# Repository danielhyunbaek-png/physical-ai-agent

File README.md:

Architecture:

The Physical AI Agent I'm currently building is a closed loop system that is made to operate a computer exactly how a human does. It uses visual feedback and physical actuations. The system runs on a discrete time loop across a macOS host and two microcontrollers.

Vision:

- Uses a fixed webcam
- Python based pipeline will capture frames at 30 fps. Each frame is deskewed using a precomputed perspective transform to map the MacBook screen to a fixed 1920x1200 pixel grid. 
- Uses OpenCV template matching for UI elements and Tesseract OCR for text extraction. 

Cognition: 

- Runs on the MacBook Pro
- Python FSM that reads perception stream and executes serial commands. 
- Goal: Under 100 ms from screen change to first physical actuation. 

Action:

-Keyboard: Using the Nuphy Air75 v3 keyboard with Blush Nano switches (45g force, 1.4 actuation).
Using the Arduino mega 2560 with 84 12V micro solenoids (10mm stroke, 5N force), housed in a custom 3D printed matrix plate. 11 cascaded 74HC595 shift resistors feeding 11 ULN2803A Darlington arrays. All powered by 12V PSU with a firmware cap of 12 solenoid activations. 

Mouse: 2 axis XY gantry system controlled by Arduino Uno. Powered by NEMA 17 steppers driven by A4988 drivers. Two SG90 hobby servos providing click actuation.

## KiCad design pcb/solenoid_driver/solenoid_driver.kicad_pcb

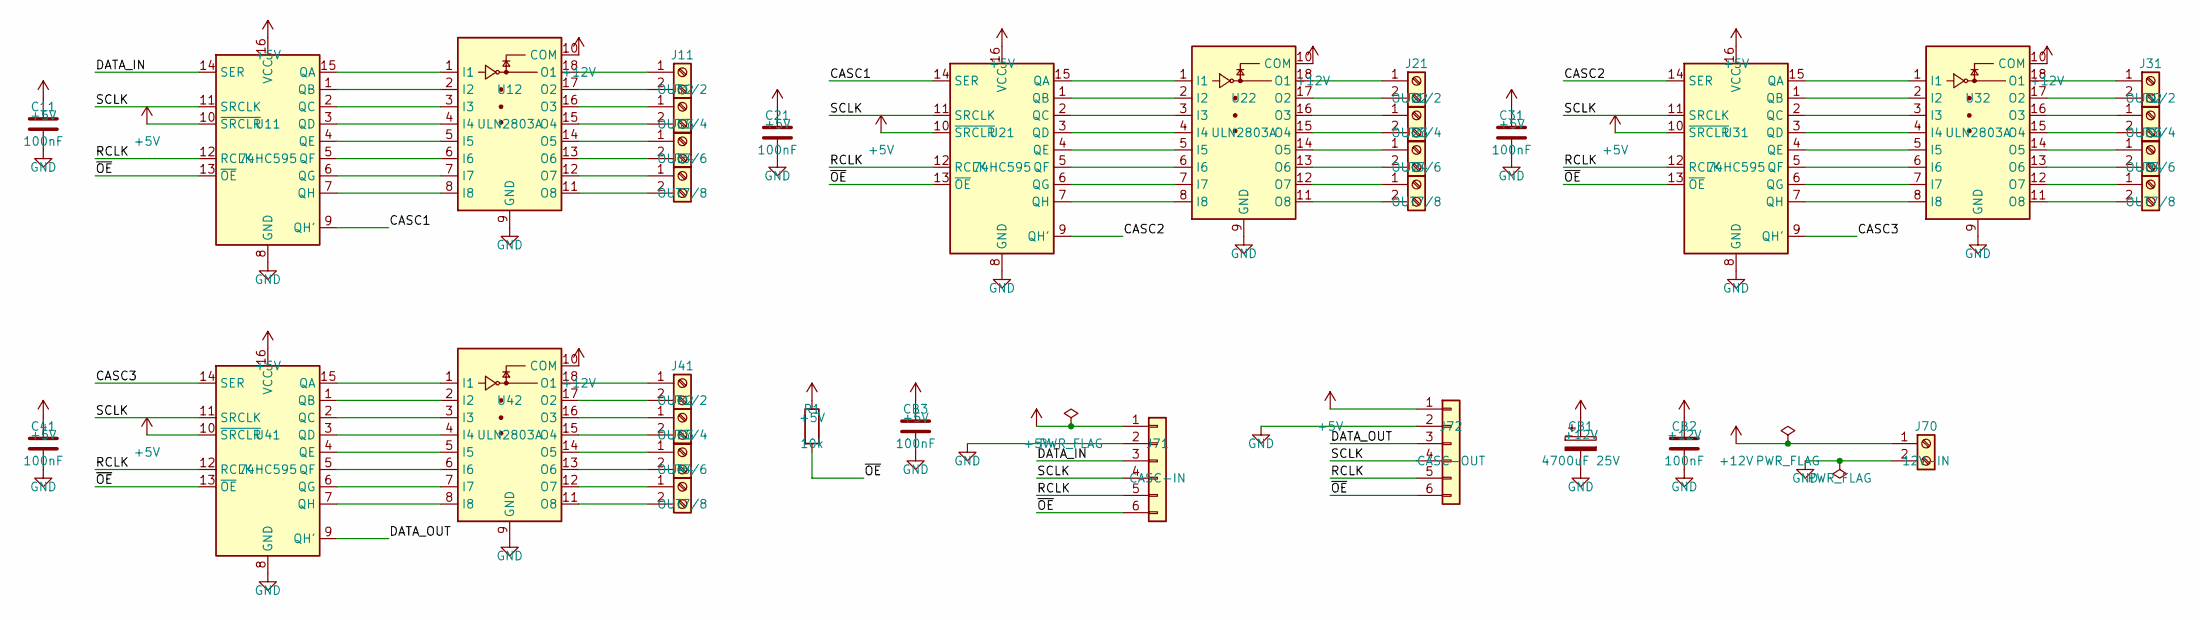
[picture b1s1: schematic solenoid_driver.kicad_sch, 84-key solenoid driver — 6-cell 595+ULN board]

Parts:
C11, C21, C31, C41: 100nF; C_Disc_D8.0mm_W5.0mm_P5.00mm
CB1: 4700uF 25V; CP_Radial_D18.0mm_P7.50mm
CB2, CB3: 100nF; C_Disc_D8.0mm_W5.0mm_P5.00mm
J11, J21, J31, J41: OUT1/2; TerminalBlock_CUI_TB007-508-02_1x02_P5.08mm_Horizontal
J12, J22, J32, J42: OUT3/4; TerminalBlock_CUI_TB007-508-02_1x02_P5.08mm_Horizontal
J13, J23, J33, J43: OUT5/6; TerminalBlock_CUI_TB007-508-02_1x02_P5.08mm_Horizontal
J14, J24, J34, J44: OUT7/8; TerminalBlock_CUI_TB007-508-02_1x02_P5.08mm_Horizontal
J70: 12V-IN; TerminalBlock_CUI_TB007-508-02_1x02_P5.08mm_Horizontal
J71: CASC-IN; PinHeader_1x06_P2.54mm_Vertical
J72: CASC-OUT; PinHeader_1x06_P2.54mm_Vertical
R1: 10k; R_Axial_DIN0207_L6.3mm_D2.5mm_P10.16mm_Horizontal
U11, U21, U31, U41: 74HC595; DIP-16_W7.62mm
U12, U22, U32, U42: ULN2803A; DIP-18_W7.62mm

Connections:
+5V: C11.1, C21.1, C31.1, C41.1, CB3.1, J71.1, J72.1, R1.1, U11.10 (~SRCLR), U11.16 (VCC), U21.10 (~SRCLR), U21.16 (VCC), U31.10 (~SRCLR), U31.16 (VCC), U41.10 (~SRCLR), U41.16 (VCC)
+12V: CB1.1, CB2.1, J70.1, U12.10 (COM), U22.10 (COM), U32.10 (COM), U42.10 (COM)
/CASC1: U11.9 (QH'), U21.14 (SER)
/CASC2: U21.9 (QH'), U31.14 (SER)
/CASC3: U31.9 (QH'), U41.14 (SER)
/DATA_IN: J71.3, U11.14 (SER)
/DATA_OUT: J72.3, U41.9 (QH')
/RCLK: J71.5, J72.5, U11.12 (RCLK), U21.12 (RCLK), U31.12 (RCLK), U41.12 (RCLK)
/SCLK: J71.4, J72.4, U11.11 (SRCLK), U21.11 (SRCLK), U31.11 (SRCLK), U41.11 (SRCLK)
/~OE: J71.6, J72.6, R1.2, U11.13 (~OE), U21.13 (~OE), U31.13 (~OE), U41.13 (~OE)
GND: C11.2, C21.2, C31.2, C41.2, CB1.2, CB2.2, CB3.2, J70.2, J71.2, J72.2, U11.8 (GND), U12.9 (GND), U21.8 (GND), U22.9 (GND), U31.8 (GND), U32.9 (GND), U41.8 (GND), U42.9 (GND)
unnamed: J11.1, U12.18 (O1)
unnamed: J11.2, U12.17 (O2)
unnamed: J12.1, U12.16 (O3)
unnamed: J12.2, U12.15 (O4)
unnamed: J13.1, U12.14 (O5)
unnamed: J13.2, U12.13 (O6)
unnamed: J14.1, U12.12 (O7)
unnamed: J14.2, U12.11 (O8)
unnamed: J21.1, U22.18 (O1)
unnamed: J21.2, U22.17 (O2)
unnamed: J22.1, U22.16 (O3)
unnamed: J22.2, U22.15 (O4)
unnamed: J23.1, U22.14 (O5)
unnamed: J23.2, U22.13 (O6)
unnamed: J24.1, U22.12 (O7)
unnamed: J24.2, U22.11 (O8)
unnamed: J31.1, U32.18 (O1)
unnamed: J31.2, U32.17 (O2)
unnamed: J32.1, U32.16 (O3)
unnamed: J32.2, U32.15 (O4)
unnamed: J33.1, U32.14 (O5)
unnamed: J33.2, U32.13 (O6)
unnamed: J34.1, U32.12 (O7)
unnamed: J34.2, U32.11 (O8)
unnamed: J41.1, U42.18 (O1)
unnamed: J41.2, U42.17 (O2)
unnamed: J42.1, U42.16 (O3)
unnamed: J42.2, U42.15 (O4)
unnamed: J43.1, U42.14 (O5)
unnamed: J43.2, U42.13 (O6)
unnamed: J44.1, U42.12 (O7)
unnamed: J44.2, U42.11 (O8)
unnamed: U11.15 (QA), U12.1 (I1)
unnamed: U11.1 (QB), U12.2 (I2)
unnamed: U11.2 (QC), U12.3 (I3)
unnamed: U11.3 (QD), U12.4 (I4)
unnamed: U11.4 (QE), U12.5 (I5)
unnamed: U11.5 (QF), U12.6 (I6)
unnamed: U11.6 (QG), U12.7 (I7)
unnamed: U11.7 (QH), U12.8 (I8)
unnamed: U21.15 (QA), U22.1 (I1)
unnamed: U21.1 (QB), U22.2 (I2)
unnamed: U21.2 (QC), U22.3 (I3)
unnamed: U21.3 (QD), U22.4 (I4)
unnamed: U21.4 (QE), U22.5 (I5)
unnamed: U21.5 (QF), U22.6 (I6)
unnamed: U21.6 (QG), U22.7 (I7)
unnamed: U21.7 (QH), U22.8 (I8)
unnamed: U31.15 (QA), U32.1 (I1)
unnamed: U31.1 (QB), U32.2 (I2)
unnamed: U31.2 (QC), U32.3 (I3)
unnamed: U31.3 (QD), U32.4 (I4)
unnamed: U31.4 (QE), U32.5 (I5)
unnamed: U31.5 (QF), U32.6 (I6)
unnamed: U31.6 (QG), U32.7 (I7)
unnamed: U31.7 (QH), U32.8 (I8)
unnamed: U41.15 (QA), U42.1 (I1)
unnamed: U41.1 (QB), U42.2 (I2)
unnamed: U41.2 (QC), U42.3 (I3)
unnamed: U41.3 (QD), U42.4 (I4)
unnamed: U41.4 (QE), U42.5 (I5)
unnamed: U41.5 (QF), U42.6 (I6)
unnamed: U41.6 (QG), U42.7 (I7)
unnamed: U41.7 (QH), U42.8 (I8)

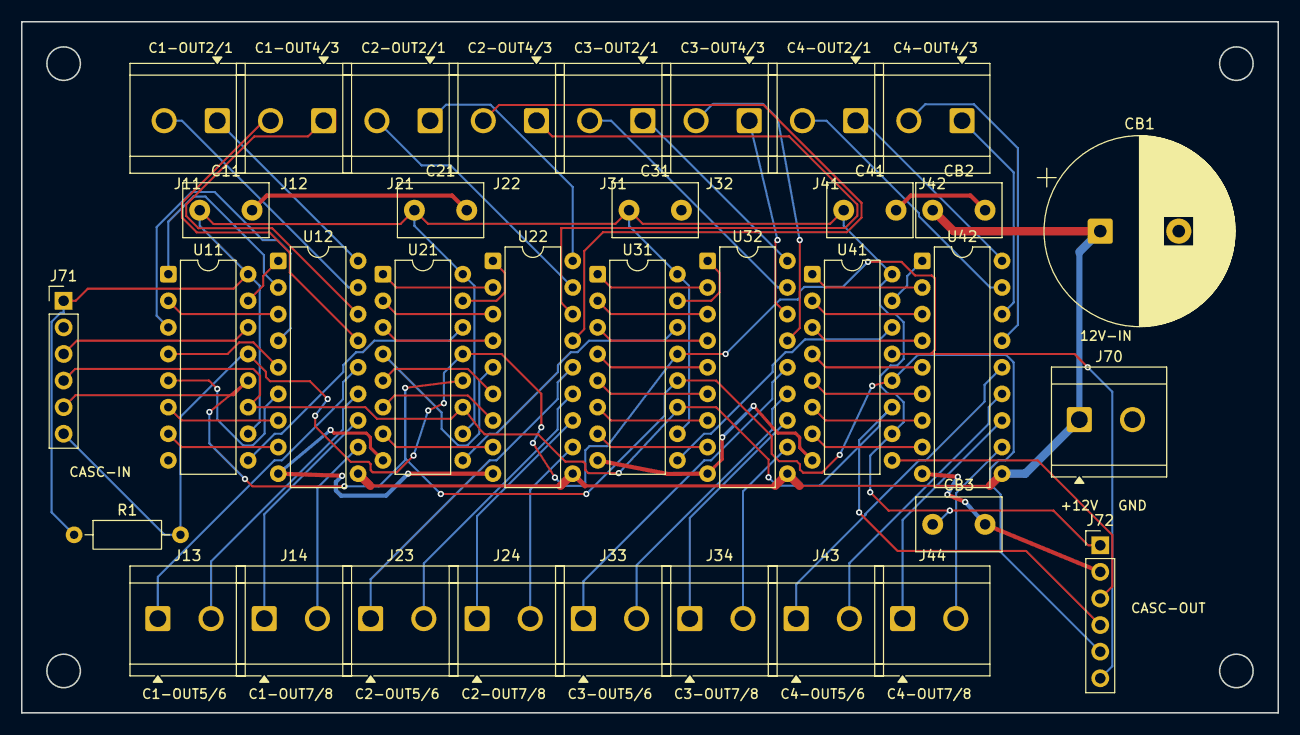
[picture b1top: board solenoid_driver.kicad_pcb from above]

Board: 2 copper layers, 120.0 x 66.0 mm, 35 parts (0 on the bottom side), 75 nets.

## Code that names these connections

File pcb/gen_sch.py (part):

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    wire(sx-10.16, sy-2.54, sx-17.78, sy-2.54)          # pin10 ~SRCLR -> +5V
    power('+5V', sx-17.78, sy-2.54)
    wire(sx-10.16, sy-10.16, sx-25.4, sy-10.16)         # pin14 SER
    label('DATA_IN' if n == 1 else f'CASC{n-1}', sx-25.4, sy-10.16)
    wire(sx-10.16, sy-5.08, sx-25.4, sy-5.08)           # pin11 SRCLK
    label('SCLK', sx-25.4, sy-5.08)
    wire(sx-10.16, sy+2.54, sx-25.4, sy+2.54)           # pin12 RCLK
    label('RCLK', sx-25.4, sy+2.54)
    wire(sx-10.16, sy+5.08, sx-25.4, sy+5.08)           # pin13 ~OE
    label('~{OE}', sx-25.4, sy+5.08)
    wire(sx+10.16, sy+12.7, sx+17.78, sy+12.7)          # pin9 QH'
    label(f'CASC{n}' if n < 6 else 'DATA_OUT', sx+17.78, sy+12.7)
    # ULN power
    power('GND', ux, uy+17.78)                          # pin9
    power('+12V', ux+10.16, uy-7.62)                    # pin10 COM (flyback)
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
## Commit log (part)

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2026-05-26 Initial commit: Add README and system architecture
2026-06-25 Initial commit — STL files, Arduino code, READMEs
2026-06-25 Remove non-essential files
2026-06-25 Keep STLs and firmware, remove docs
